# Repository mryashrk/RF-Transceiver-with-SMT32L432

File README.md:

# RF-Transceiver-with-SMT32L432

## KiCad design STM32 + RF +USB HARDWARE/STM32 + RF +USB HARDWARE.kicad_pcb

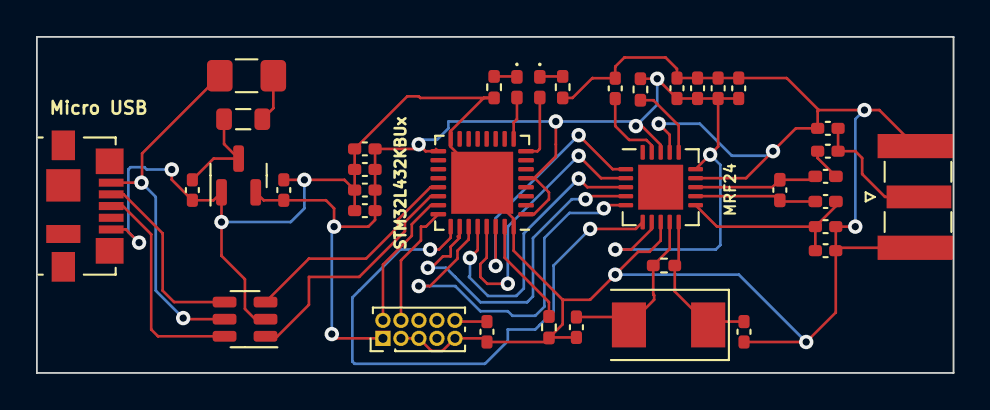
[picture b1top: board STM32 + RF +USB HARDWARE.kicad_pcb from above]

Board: 2 copper layers, 50.9 x 18.7 mm, 38 parts (0 on the bottom side), 32 nets.

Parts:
C1, C2: 10u; C_0402_1005Metric_Pad0.74x0.62mm_HandSolder
C3: 1U; C_0402_1005Metric_Pad0.74x0.62mm_HandSolder
C4, C5, C6: 100N; C_0402_1005Metric_Pad0.74x0.62mm_HandSolder
C7: 33n; C_0402_1005Metric_Pad0.74x0.62mm_HandSolder
C8, C9, C10, C11: 10n; C_0402_1005Metric_Pad0.74x0.62mm_HandSolder
C12, C13: 12p; C_0402_1005Metric_Pad0.74x0.62mm_HandSolder
C14: 1p; C_0402_1005Metric_Pad0.74x0.62mm_HandSolder
C15: 1.5p; C_0402_1005Metric_Pad0.74x0.62mm_HandSolder
C16: 4.7p; C_0402_1005Metric_Pad0.74x0.62mm_HandSolder
C17: 2.2n; C_0402_1005Metric_Pad0.74x0.62mm_HandSolder
C18: 100n; C_0402_1005Metric_Pad0.74x0.62mm_HandSolder
D1, D2: LED; LED_0402_1005Metric_Pad0.77x0.64mm_HandSolder
F1: 100mA; Fuse_1206_3216Metric_Pad1.42x1.75mm_HandSolder
FB1: 100MHZ; L_0805_2012Metric
J1: Micro USB; USB_Micro-B_Molex_47346-0001
J2: Conn_Coaxial; SMA_Samtec_SMA-J-P-X-ST-EM1_EdgeMount
J3: Conn_02x05_Odd_Even; PinHeader_2x05_P1.00mm_Vertical
L1: 8.2n; L_0402_1005Metric_Pad0.77x0.64mm_HandSolder
L2: 3.3n; L_0402_1005Metric_Pad0.77x0.64mm_HandSolder
L3: 2.7n; L_0402_1005Metric_Pad0.77x0.64mm_HandSolder
R1, R2: 2.2K; R_0402_1005Metric_Pad0.72x0.64mm_HandSolder
R3: 10K; R_0402_1005Metric_Pad0.72x0.64mm_HandSolder
R4: 22k; R_0402_1005Metric_Pad0.72x0.64mm_HandSolder
R5: 1M; R_0402_1005Metric_Pad0.72x0.64mm_HandSolder
U1: STM32L432KBUx; QFN-32-1EP_5x5mm_P0.5mm_EP3.45x3.45mm
U2: XC6206PxxxMR; SOT-23
U3: USBLC6-2SC6; SOT-23-6
U4: nRF24L01P; QFN-20-1EP_4x4mm_P0.5mm_EP2.5x2.5mm
Y1: 16MHz; Crystal_SMD_0603-2Pin_6.0x3.5mm

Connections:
+3.3V: C2.1, C3.1, C4.1, C5.1, C6.1, C8.1, C9.1, C10.1, C11.1, J3.1, R4.1, U1.1 (VDD), U1.5 (VDDA), U1.17 (VDD), U2.2 (VO), U4.7 (VDD), U4.15 (VDD), U4.18 (VDD)
+5V: F1.1, J1.1 (VBUS), U3.5 (VBUS)
/D+: U1.22 (PA12), U3.1 (I/O1)
/D-: U1.21 (PA11), U3.3 (I/O2)
/HRF_ANT1: L1.2, L3.1, U4.12 (ANT1)
/HRF_ANT2: L1.1, L2.1, U4.13 (ANT2)
/HRF_CE: U1.30 (PB7), U4.1 (CE)
/HRF_IRQ: U1.25 (PA15), U4.6 (IRQ)
/HRF_VDD_PA: C16.1, C17.1, L3.2, U4.11 (VDD_PA)
/HRF_XC1: C12.1, R5.1, U4.10 (XC1), Y1.1
/HRF_XC2: C13.1, R5.2, U4.9 (XC2), Y1.2
/SPI3_ICS: U1.29 (PB6), U4.2 (CSN)
/SPI3_MISO: U1.27 (PB4), U4.5 (MISO)
/SPI3_MOSI: U1.26 (PB3), U4.4 (MOSI)
/SPI3_SCK: U1.28 (PB5), U4.3 (SCK)
/SWCLK: J3.4, U1.24 (PA14)
/SWDIO: J3.2, U1.23 (PA13)
/USB_CON_D+: J1.3 (D+), U3.6 (I/O1)
/USB_CON_D-: J1.2 (D-), U3.4 (I/O2)
GND: C1.2, C2.2, C3.2, C4.2, C5.2, C6.2, C7.2, C8.2, C9.2, C10.2, C11.2, C12.2, C13.2, C14.2, C16.2, C17.2, C18.2, J1.5 (GND), J2.2 (Ext), J3.3, J3.5, J3.9, R1.2, R2.2, R3.2, U1.16 (VSS), U1.32 (VSS), U1.33 (VSS), U2.1 (GND), U3.2 (GND), U4.8 (VSS), U4.14 (VSS), U4.17 (VSS), U4.20 (VSS)
unnamed: C15.1, L2.2
unnamed: D1.2 (A), U1.9 (PA3)
unnamed: D1.1 (K), R1.1
unnamed: D2.2 (A), U1.8 (PA2)
unnamed: D2.1 (K), R2.1
unnamed: F1.2, FB1.1
unnamed: C14.1, C15.2, J2.1 (In)
unnamed: C18.1, J3.10
unnamed: R3.1, U1.31 (PH3)
unnamed: C1.1, FB1.2, U2.3 (VI)
unnamed: C7.1, U4.19 (DVDD)
unnamed: R4.2, U4.16 (IREF)
